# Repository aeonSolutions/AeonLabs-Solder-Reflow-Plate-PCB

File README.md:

[PCB-Prototyping-Catalogue](https://github.com/aeonSolutions/PCB-Prototyping-Catalogue)  >>  [DIY & Maker](https://github.com/aeonSolutions/PCB-Prototyping-Catalogue/blob/main/DIY-Maker/README.md)  >> Solder Reflow Plate PCB

<br>

<br />

# Solder Reflow Plate PCB
 Improved Kicad PCB schematics for a DIY Solder Reflow Plate from the original pcb schematic by [AfterEarthLTD](https://github.com/AfterEarthLTD/Solder-Reflow-Plate). AeonLabs Solder Reflow Plate features a Nextion 3.2" LCD Touch and a ESP32 WROOM32 for WiFi and Bluetooth connectivity. 

*Don't forget to LIKE , SHARE and subscribe the free whatsApp group* and if you liked this PCB consider buying me a cup of coffee. Links below.

### Status
  Revision 1.3 needs to cross TX/RX pads or else fails with "no serial data ..."

 revision 2.0 waiting to be tested.

If you have already tested this PCB send me a message.

## Versions
### AeonLabs improved Hot Solder Reflow Plate
- revision 2.x (ToDo)
  - Firmware code for the ESP32 WROOM32 and for the Nextion 3.2" LCD Touch on this Solder Reflow Plate
  - Android App to view and control the hot plate temperature

- revision 2.0
  - Serial TX/RX track lines correction.
  - Added an ON/ OFF switch 
  - Redesigned and new 5.0V and 3.3V power managment for more than 90% efficiency . No more hot LDOs on the PCB! 
 
- revison 1.x
  - Upgraded to ZLDO1117 voltage regulators with copper heat dissipation area
  - ESP32 MCU with BLE and WiFi
  - 2x Temperature seensors for improved management of Reflow temperature
  - 12VDC (5A Minimum)
  - 5.5mm x 2.5mm Barrel Jack
  - With corner M7.5 holes for placement of an aluminium plate on top of the PCB for extended lifetime and durability
  - Electronic components placed on the bottom side for extended lifetime and improved duraility
  - Aluminium plate can now be exported as Gerber to [FlatCAM](http://flatcam.org) and drilled using [Candle](https://github.com/Denvi/Candle) 

<p align="center">
  
  </p>

### *FlatCAM settings*
 
One can CNC the aluminium base plate on any GBRL CNC machine like this one on AliExpress [here](https://s.click.aliexpress.com/e/_AOOXQ7). Don't forget to use a thin lubricating oil for improved results. 
 
  - Feed Rate: 0.3-0.5 units/min
  - Depth pass: 1.1 mm or 0.04331 inch (unless your setup your CNC with Z-height correction; for a 8mm thick aluminium plate)
  - Tool [CNC Single Flute Milling cutters for Aluminum](https://www.aliexpress.com/item/1005004188243213.html?spm=a2g0o.cart.0.0.3cb23c00L4Ibog&mp=1): 2mm or 0.07874 inch
  - pass overlap: 0.0
  
 ________________________________________________________________________________________________________________

### Regular Hot Solder Reflow Plate as seen on GreatScott
- revision 1.0
  - 120mm x 70mm (Bigger hot plate dimensions)
  - 12VDC (5A Minimum)
  - 5.5mm x 2.5mm Barrel Jack
  - 0.91" OLED Display
  - Atmel Mega 328P MCU (this version includes a crystal for programming)
  - With corner M2.5 holes for placement of an aluminium plate on top of the PCB for extended lifetime and durability.

## As Seen On GreatScott! 
This is the Gerber & KiCad files for the Youtuber GreatScott! video "The Best way to reflow solder? Hot Plate to the rescue! DIY or Buy"
Check it out here - [The Best way to reflow solder? Hot Plate to the rescue! DIY or Buy](https://www.youtube.com/watch?v=QarizoUnRfk)

You have 2 options:

Download this repository for the KiCad Files or, download the Gerber files in the release section of this repository

### alternatively if you do not want to build a PCB by yourself, you can buy here:

<p align="center">
  
</p>

The price will be around 30eur plus postage fees.
(I will also deliver the assembled PCB with all the components in place at an aditonal cost).

## Liked it ? Get a Free PCB for yourself
Send me your device or hardware and i will design a custom PCB for it. Free of charge. Contact-me on WhatsApp or email for more info. 

|  | *Don't forget to **LIKE** , **SHARE** and **subscribe** the free chat groups* and if you downloaded one of AeonLabs's PCBs consider sponsor  any open hardware project with a donation or a cup of coffee. Links on the top, right side pane and below. |
|-------------|------|

<br />
<br />

## Q&A WhatsApp/Telegram Groups
|  | Subscribe to the WhatsApp or Telegram channel to get latest information about any of this KiCad projects and get help. Or simply like this kind of projects and want to stay updated with the latest research ideas and prototypes during the day and week.   |
|-------------|------|

<br />
<br />
<br />

## Youtube Channel
|  | Subscribe to my Youtube channel for PCB assembly instruction or any other related to Artificial Intelligence, Smart devices and robotics. Link to the channel [here](https://www.youtube.com/channel/UCAewCBpMRPGCyFc1ET5CHJw). My most recent video is .... |
|-------------|------|

#### PCB Parts list:
- 1x AMS1117-3.3, sold on AliExpress [here](https://s.click.aliexpress.com/e/_AOIVLN)
- 1x AMS1117-5.0, sold on AliExpress [here](https://s.click.aliexpress.com/e/_AOIVLN)
- 1x FUSE SMD 1206 5A, sold on AliExpress [here](https://s.click.aliexpress.com/e/_A8yVgJ)
- 1x MM1Z24, sold on AliExpress [here](https://www.aliexpress.com/item/1005003538876461.html?spm=a2g0o.order_list.0.0.2bb91802tqEyK1)
- Barrel Jack, sold on AliExpress [here](https://s.click.aliexpress.com/e/_As3F2L)
- 1x FPC 1x4 pin 1mm pitch horizontal, sold on AliExpress [here](https://s.click.aliexpress.com/e/_ASMTDp)
- 1x FPC flat cable 1mm pitch 4 pin, sold on AliExpress [here](https://s.click.aliexpress.com/e/_9js0C7)
- 1x DSR1M, sold on AliExpress [here](https://s.click.aliexpress.com/e/_9JQobh)
- 1x SMAJ18A, sold on AliExpress [here](https://s.click.aliexpress.com/e/_9zW0DN)
- 2x LMT85LP, sold on AliExpress [here](https://www.aliexpress.com/item/1005003755656556.html?spm=a2g0o.order_list.0.0.42ba1802MVKTRu)
- 1x UMW30N06, sold on AliExpress [here](https://www.aliexpress.com/item/4000687585069.html?spm=a2g0o.order_list.0.0.2bb91802tqEyK1)
- 1x ESP32 WROOM32, sold on AliExpress [here](https://www.aliexpress.com/item/32912371635.html?spm=a2g0o.productlist.0.0.1c737b00qtI6F1&algo_pvid=2b9d3923-cad6-4894-abba-bcbe1659aab6&algo_exp_id=2b9d3923-cad6-4894-abba-bcbe1659aab6-0&pdp_ext_f=%7B"sku_id"%3A"65986896288"%7D&pdp_npi=2%40dis%21EUR%21%212.27%21%21%21%21%21%400bb0622916528901078995704e092a%2165986896288%21sea)
- 1x NEXTION 3.2" LCD Touch, sold on AliExpress [here](https://www.aliexpress.com/item/32678581956.html?spm=a2g0o.productlist.0.0.16f46e8cmt3XbA&algo_pvid=657314cc-0888-4621-8795-71fcd735d410&algo_exp_id=657314cc-0888-4621-8795-71fcd735d410-2&pdp_ext_f=%7B%22sku_id%22%3A%2210000003437337029%22%7D&pdp_npi=2%40dis%21EUR%21%2126.15%21%21%21%21%21%40210318b916528902149054769e34ce%2110000003437337029%21sea)

<br />
<br />

## Author

You can get in touch with me on my LinkedIn Profile:

#### Miguel Tomas

You can also follow my GitHub Profile to stay updated about my latest projects: 

<br>

**Hire me** <br>
See [here](https://github.com/aeonSolutions/PCB-Prototyping-Catalogue/wiki/How-to-Hire-AeonLabs) how to hire AeonLabs.

<br>

### Be supportive of my dedication and work towards technology education and buy me a cup of coffee
The PCB design Files I provide here for anyone to use are free. If you like this Smart Device or use it, please consider buying me a cup of coffee, a slice of pizza or a book to help me study, eat and think new PCB design files.

<p align="center">
    
</p>

### Make a donation on PayPal
Make a donation on PayPal and get a TAX refund*.

<p align="center">
    
</p>

### Support all these open hardware projects and become a GitHub sponsor  
Liked any of my PCB KiCad Designs? Help and Support my open work to all by becoming a GitHub sponsor.

<p align="center">

</p>

# 

### License

Before proceeding to download any of AeonLabs software solutions for open-source development and/or PCB hardware electronics development make sure you are choosing the right license for your project. See [AeonLabs Solutions for Open Hardware & Source Development](https://github.com/aeonSolutions/PCB-Prototyping-Catalogue/wiki/AeonLabs-Solutions-for-Open-Hardware-&-Source-Development) for more information.

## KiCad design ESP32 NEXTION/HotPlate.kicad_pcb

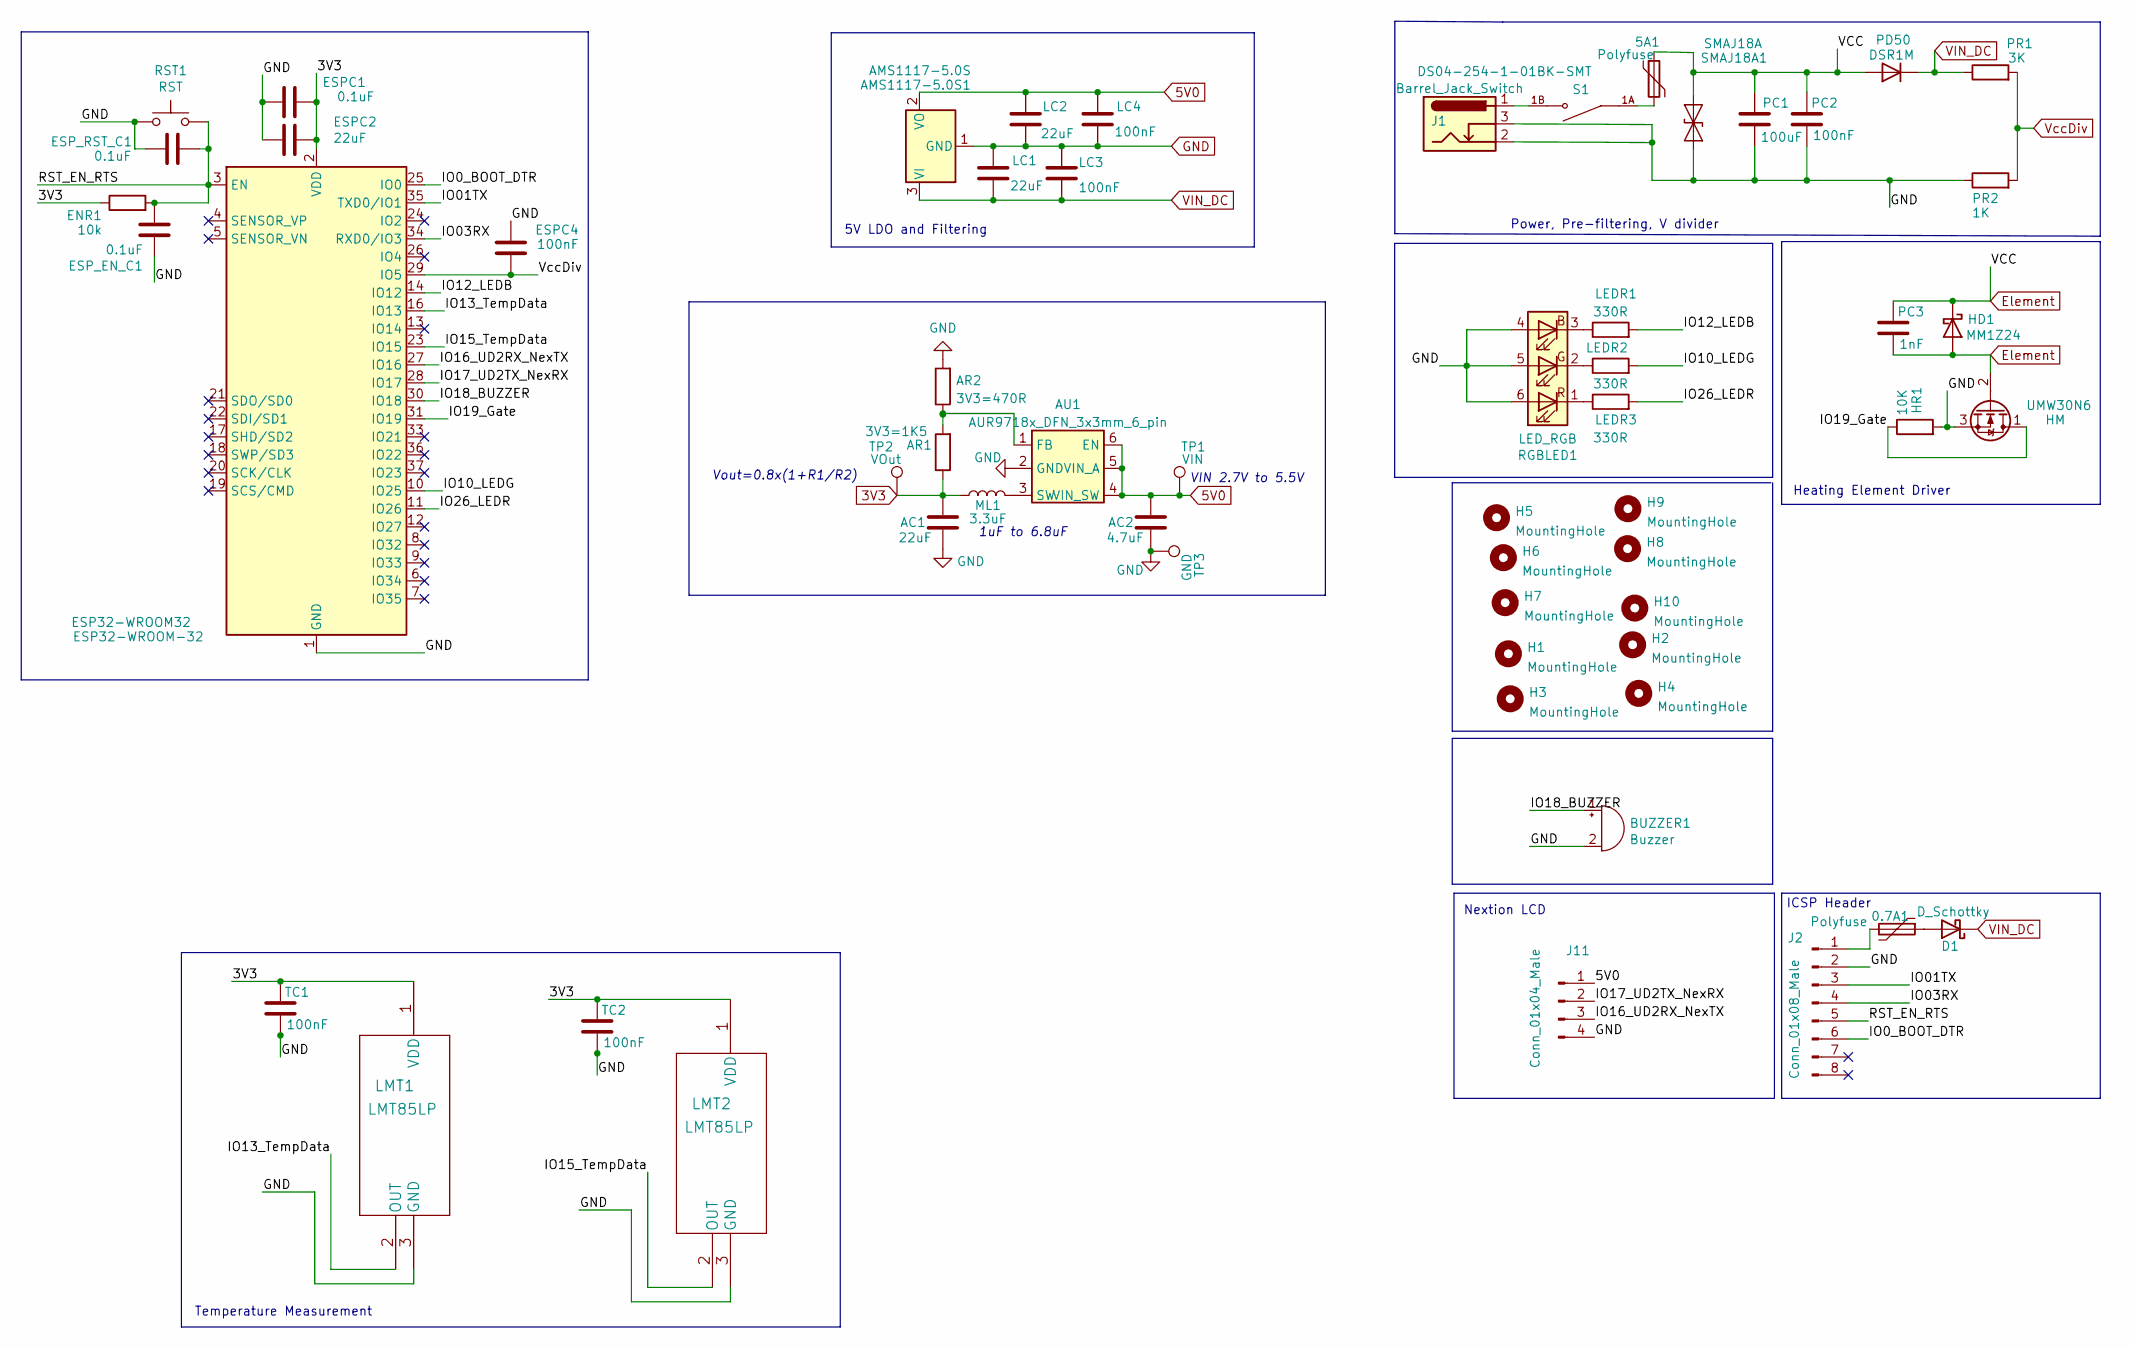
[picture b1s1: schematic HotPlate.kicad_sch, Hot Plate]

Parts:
0.7A1, 5A1: Polyfuse; Fuse_1206_3216Metric
AC1: 22uF; C_0805_2012Metric_Pad1.18x1.45mm_HandSolder
AC2: 4.7uF; C_0805_2012Metric_Pad1.18x1.45mm_HandSolder
AMS1117-5.0S1: AMS1117-5.0S; SOT-223-3_TabPin2
AR1: 3V3=1K5; R_0805_2012Metric_Pad1.20x1.40mm_HandSolder
AR2: 3V3=470R; R_0805_2012Metric_Pad1.20x1.40mm_HandSolder
AU1: AUR9718x_DFN_3x3mm_6_pin; AUR9718 3x3mm 6 pin
BUZZER1: Buzzer; MagneticBuzzer_Kobitone_254-EMB84Q-RO
D1: D_Schottky; D_1210_3225Metric_Pad1.42x2.65mm_HandSolder
ENR1: 10k; R_1206_3216Metric
ESP32-WROOM32: ESP32-WROOM-32
ESPC1: 0.1uF; C_1206_3216Metric
ESPC2: 22uF; C_1206_3216Metric
ESPC4: 100nF; C_1206_3216Metric
ESP_EN_C1: 0.1uF; C_1206_3216Metric
ESP_RST_C1: 0.1uF; C_1206_3216Metric
H1, H2, H3, H4: MountingHole; MountingHole_3.2mm_M3
H5, H6, H7, H8, H9, H10: MountingHole; MountingHole_8.4mm_M8
HD1: MM1Z24; D_SOD-123
HR1: 10K; C_1206_3216Metric_Pad1.33x1.80mm_HandSolder
J1: Barrel_Jack_Switch; BarrelJack_Horizontal
J2: Conn_01x08_Male; SOIC_clipProgSmall
J11: Conn_01x04_Male; Molex_200528-0040_1x04-1MP_P1.00mm_Horizontal
LC1, LC2: 22uF; C_1206_3216Metric_Pad1.33x1.80mm_HandSolder
LC3, LC4: 100nF; C_1206_3216Metric_Pad1.33x1.80mm_HandSolder
LEDR1, LEDR2, LEDR3: 330R; R_1206_3216Metric
LMT1, LMT2: LMT85LP
ML1: 3.3uF; L_1210_3225Metric
PC1: 100uF; CP_Elec_10x12.5
PC2: 100nF; C_1206_3216Metric_Pad1.33x1.80mm_HandSolder
PC3: 1nF; C_1206_3216Metric_Pad1.33x1.80mm_HandSolder
PD50: DSR1M; D_SOD-123F
PR1: 3K; C_1206_3216Metric_Pad1.33x1.80mm_HandSolder
PR2: 1K; C_1206_3216Metric_Pad1.33x1.80mm_HandSolder
RGBLED1: LED_RGB; LED_RGB_5050-6
RST1: RST; SW_Push_SPST_NO_Alps_SKRK
S1: DS04-254-1-01BK-SMT; Side Switch 3pin 5A; PARTREV V0.0
SMAJ18A1: SMAJ18A; D_1210_3225Metric_Pad1.42x2.65mm_HandSolder
TC1, TC2: 100nF; C_1206_3216Metric_Pad1.33x1.80mm_HandSolder
TP1: VIN; TestPoint_Pad_D1.0mm
TP2: VOut; TestPoint_Pad_D1.0mm
TP3: GND; TestPoint_Pad_D1.0mm
UMW30N6: HM; TO-252-2

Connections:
3V3: AC1.1, AR1.1, ENR1.1, ESP32-WROOM32.2 (VDD), ESPC1.1, ESPC2.1, LMT1.1 (VDD), LMT2.1 (VDD), ML1.1, TC1.1, TC2.1, TP2.1
5V0: AC2.1, AMS1117-5.0S1.2 (VO), AU1.4 (VIN_SW), AU1.5 (VIN_A), AU1.6 (EN), J11.1, LC2.1, LC4.1, TP1.1
/IO0_BOOT_DTR: ESP32-WROOM32.25 (IO0), J2.6
/IO01TX: ESP32-WROOM32.35 (TXD0/IO1), J2.3
/IO03RX: ESP32-WROOM32.34 (RXD0/IO3), J2.4
/IO10_LEDG: ESP32-WROOM32.10 (IO25), LEDR2.2
/IO12_LEDB: ESP32-WROOM32.14 (IO12), LEDR1.2
/IO13_TempData: ESP32-WROOM32.16 (IO13), LMT1.2 (OUT)
/IO15_TempData: ESP32-WROOM32.23 (IO15), LMT2.2 (OUT)
/IO16_UD2RX_NexTX: ESP32-WROOM32.27 (IO16), J11.3
/IO17_UD2TX_NexRX: ESP32-WROOM32.28 (IO17), J11.2
/IO18_BUZZER: BUZZER1.1 (-), ESP32-WROOM32.30 (IO18)
/IO19_Gate: ESP32-WROOM32.31 (IO19), HR1.1, UMW30N6.1 (D)
/IO26_LEDR: ESP32-WROOM32.11 (IO26), LEDR3.2
/RST_EN_RTS: ENR1.2, ESP32-WROOM32.3 (EN), ESP_EN_C1.2, ESP_RST_C1.1, J2.5, RST1.2
Element: 5A1.1, HD1.1 (K), HD1.2 (A), PC1.1, PC2.1, PC3.1, PC3.2, PD50.2 (A), SMAJ18A1.1 (A1), UMW30N6.2 (G)
GND: AC1.2, AC2.2, AMS1117-5.0S1.1 (GND), AR2.2, AU1.2 (GND), BUZZER1.2 (+), ESP32-WROOM32.1 (GND), ESP32-WROOM32.15 (GND), ESP32-WROOM32.38 (GND), ESP32-WROOM32.39 (GND), ESPC1.2, ESPC2.2, ESPC4.2, ESP_EN_C1.1, ESP_RST_C1.2, HR1.2, J1.2, J1.3, J2.2, J11.4, LC1.1, LC2.2, LC3.1, LC4.2, LMT1.3 (GND), LMT2.3 (GND), PC1.2, PC2.2, PR2.1, RGBLED1.4 (BA), RGBLED1.5 (GA), RGBLED1.6 (RA), RST1.1, SMAJ18A1.2 (A2), TC1.2, TC2.2, TP3.1, UMW30N6.3 (S)
unnamed: 0.7A1.1, D1.2 (A)
unnamed: 0.7A1.2, J2.1
unnamed: 5A1.2, S1.1A
unnamed: AR1.2, AR2.1, AU1.1 (FB)
unnamed: AU1.3 (SW), ML1.2
unnamed: J1.1, S1.1B
unnamed: LEDR1.1, RGBLED1.3 (BK)
unnamed: LEDR2.1, RGBLED1.2 (GK)
unnamed: LEDR3.1, RGBLED1.1 (RK)
VIN_DC: AMS1117-5.0S1.3 (VI), D1.1 (K), LC1.2, LC3.2, PD50.1 (K), PR1.1
VccDiv: ESP32-WROOM32.29 (IO5), ESPC4.1, PR1.2, PR2.2

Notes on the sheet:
Power, Pre-filtering, V divider
ICSP Header
Vout=0.8x(1+R1/R2)
Temperature Measurement
Heating Element Driver
1uF to 6.8uF
5V LDO and Filtering
Nextion LCD
VIN 2.7V to 5.5V

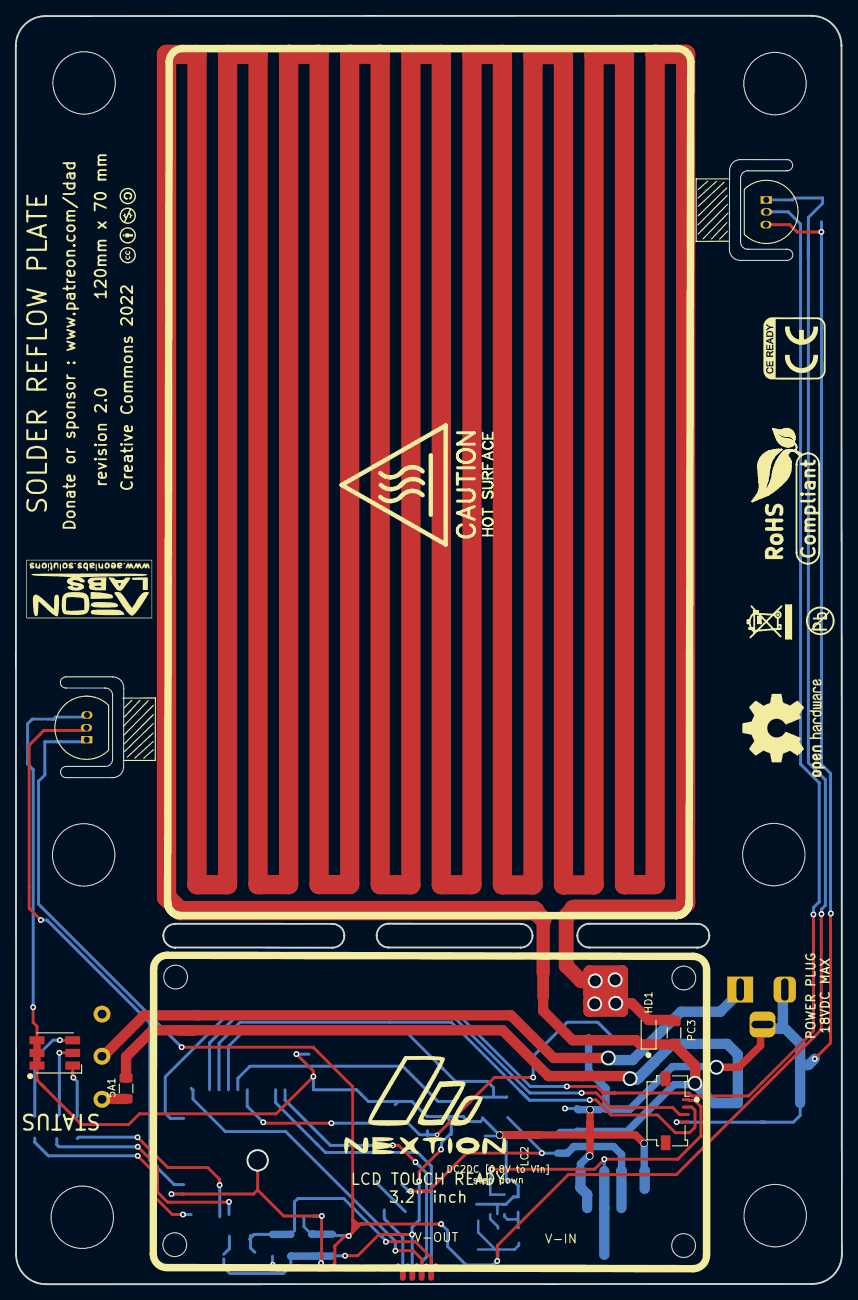
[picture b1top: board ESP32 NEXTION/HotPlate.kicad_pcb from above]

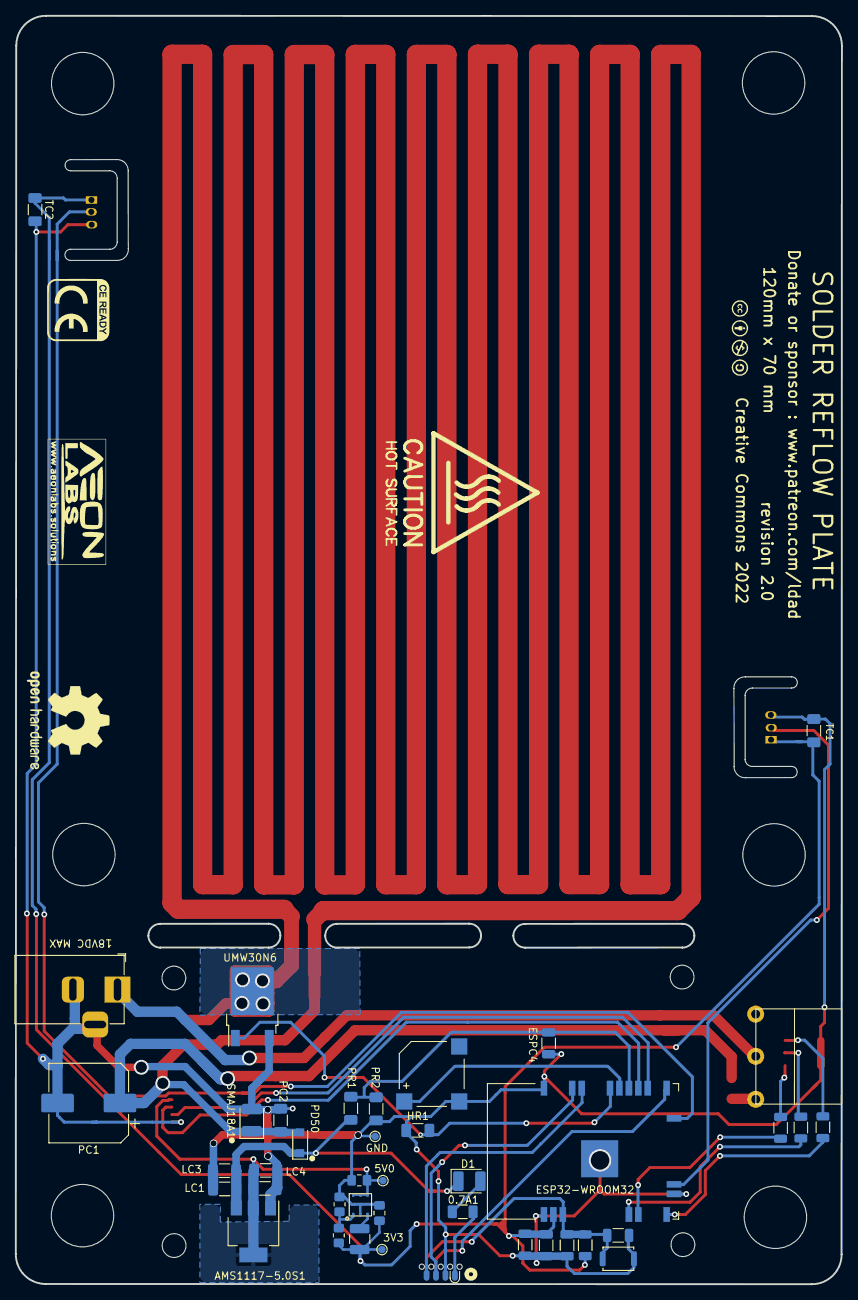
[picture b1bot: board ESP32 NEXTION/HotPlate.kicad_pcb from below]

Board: 6 copper layers, 111.2 x 170.7 mm, 61 parts (41 on the bottom side), 28 nets.

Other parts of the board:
Sign-PbFree: LOGO_PBFREE
Sign-RecycleBin: LOGO_RECYCLEBIN_1
Sign-RoHS: LOGO_ROHS_1

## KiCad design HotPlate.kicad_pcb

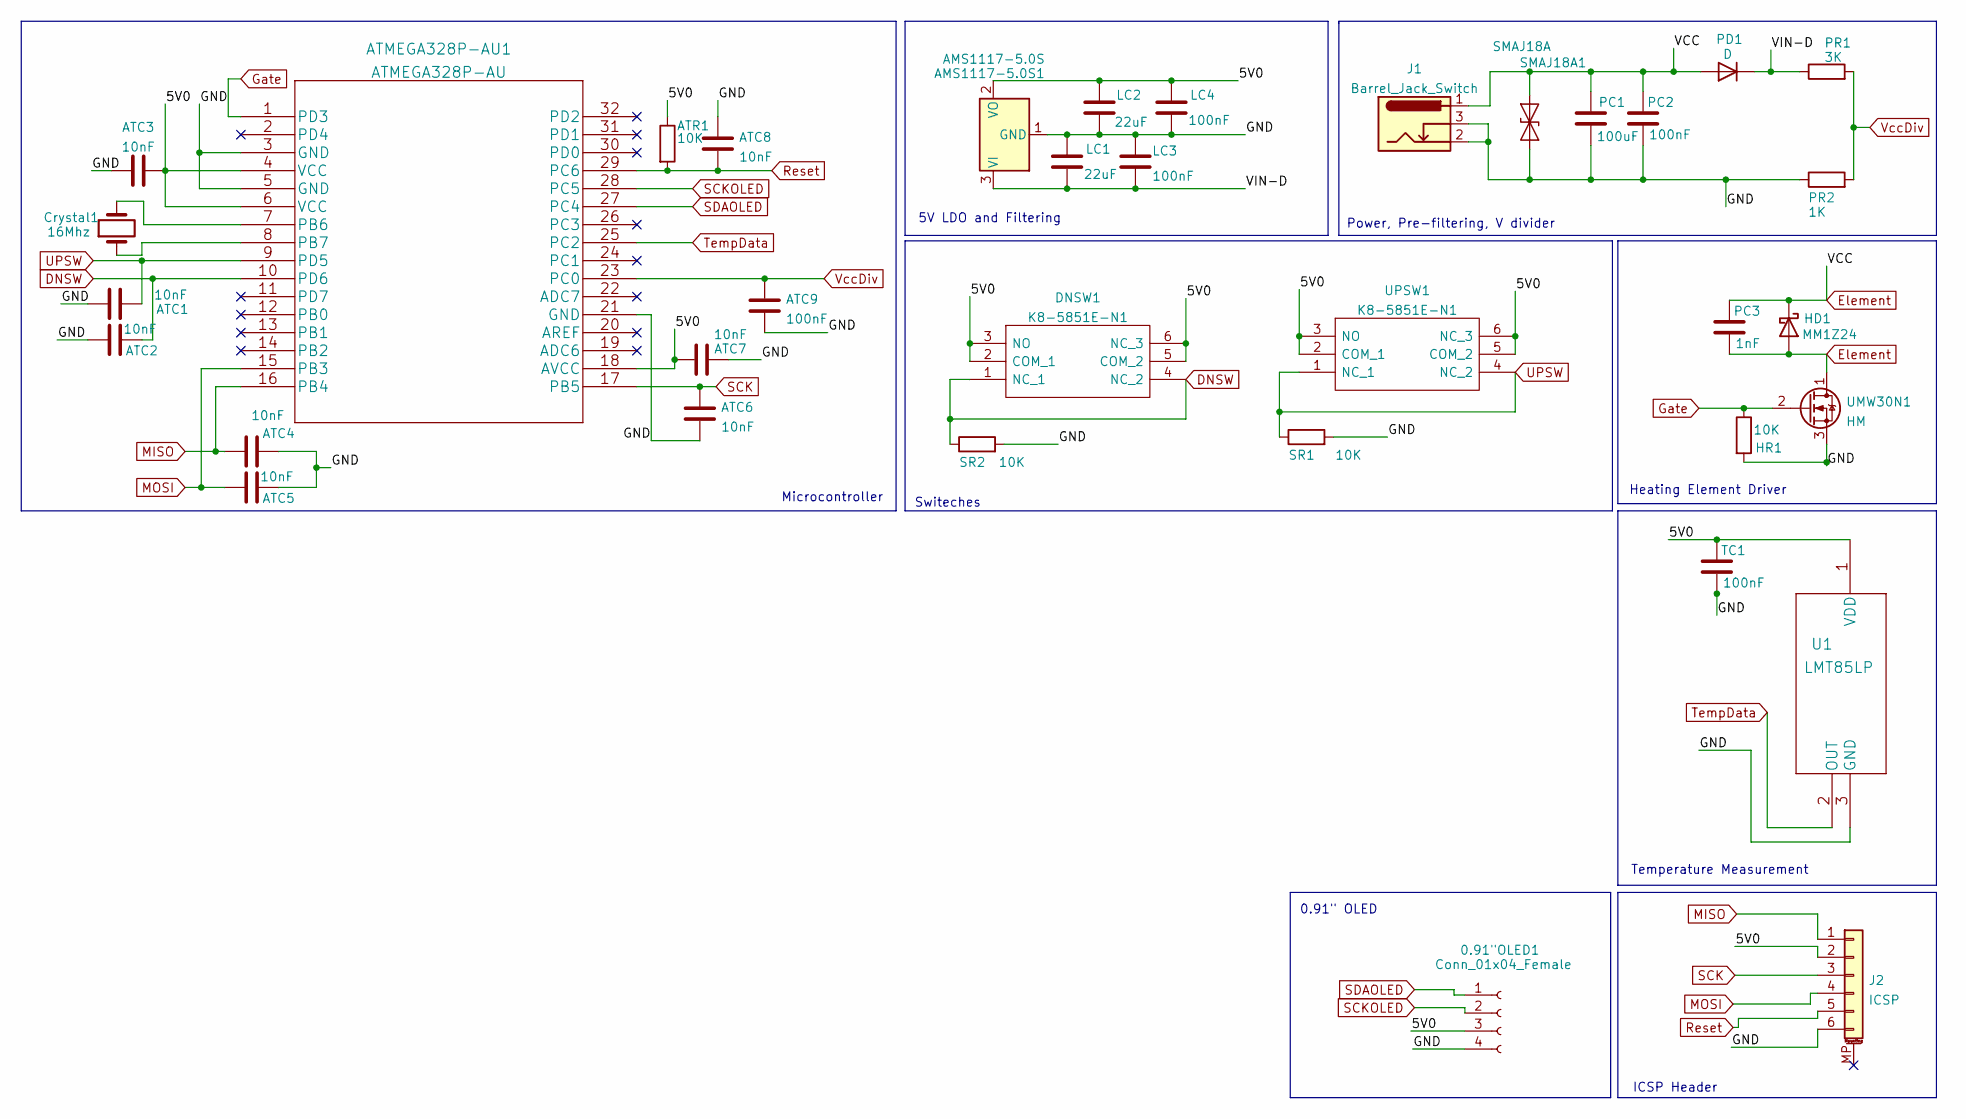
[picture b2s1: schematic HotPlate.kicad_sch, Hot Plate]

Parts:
0.91"OLED1: Conn_01x04_Female; SSD1306-0.91-OLED-4pin-128x32
AMS1117-5.0S1: AMS1117-5.0S; SOT-223-3_TabPin2
ATC1, ATC2, ATC3, ATC4, ATC5, ATC6, ATC7, ATC8: 10nF; C_1206_3216Metric_Pad1.33x1.80mm_HandSolder
ATC9: 100nF; C_1206_3216Metric_Pad1.33x1.80mm_HandSolder
ATMEGA328P-AU1: ATMEGA328P-AU
ATR1: 10K; R_1206_3216Metric
Crystal1: 16Mhz; Crystal_SMD_5032-2Pin_5.0x3.2mm
DNSW1: K8-5851E-N1; K85851EN1; Manufacturer_Part_Number K8-5851E-N1
HD1: MM1Z24
HR1: 10K; C_1206_3216Metric_Pad1.33x1.80mm_HandSolder
J1: Barrel_Jack_Switch; BarrelJack_Horizontal
J2: ICSP; PinHeader_2x03_P2.54mm_Vertical
LC1, LC2: 22uF; C_1206_3216Metric_Pad1.33x1.80mm_HandSolder
LC3, LC4: 100nF; C_1206_3216Metric_Pad1.33x1.80mm_HandSolder
PC1: 100uF; CP_Elec_6.3x5.9
PC2: 100nF; C_1206_3216Metric_Pad1.33x1.80mm_HandSolder
PC3: 1nF; C_1206_3216Metric_Pad1.33x1.80mm_HandSolder
PD1: D; D_SOD-123
PR1: 3K; C_1206_3216Metric_Pad1.33x1.80mm_HandSolder
PR2: 1K; C_1206_3216Metric_Pad1.33x1.80mm_HandSolder
SMAJ18A1: SMAJ18A; D_SOD-123
SR1, SR2: 10K; C_1206_3216Metric_Pad1.33x1.80mm_HandSolder
TC1: 100nF; C_1206_3216Metric_Pad1.33x1.80mm_HandSolder
U1: LMT85LP
UMW30N1: HM
UPSW1: K8-5851E-N1; K85851EN1; Manufacturer_Part_Number K8-5851E-N1

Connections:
/5V0: 0.91"OLED1.3, AMS1117-5.0S1.2 (VO), ATC3.2, ATC7.1, ATMEGA328P-AU1.4 (VCC), ATMEGA328P-AU1.6 (VCC), ATMEGA328P-AU1.18 (AVCC), ATR1.1, DNSW1.2 (COM_1), DNSW1.3 (NO), DNSW1.5 (COM_2), DNSW1.6 (NC_3), J2.2, LC2.1, LC4.1, TC1.1, U1.1 (VDD), UPSW1.2 (COM_1), UPSW1.3 (NO), UPSW1.5 (COM_2), UPSW1.6 (NC_3)
/GND: 0.91"OLED1.4, AMS1117-5.0S1.1 (GND), ATC1.1, ATC2.1, ATC3.1, ATC4.2, ATC5.2, ATC6.2, ATC7.2, ATC8.1, ATC9.2, ATMEGA328P-AU1.3 (GND), ATMEGA328P-AU1.5 (GND), ATMEGA328P-AU1.21 (GND), HR1.2, J1.2, J1.3, J2.6, LC1.1, LC2.2, LC3.1, LC4.2, PC1.2, PC2.2, PR2.1, SMAJ18A1.1 (A1), SR1.2, SR2.2, TC1.2, U1.3 (GND), UMW30N1.3 (S)
/VIN-D: AMS1117-5.0S1.3 (VI), LC1.2, LC3.2, PD1.1 (K), PR1.1
DNSW: ATC2.2, ATMEGA328P-AU1.10 (PD6), DNSW1.1 (NC_1), DNSW1.4 (NC_2), SR2.1
Element: HD1.1 (K), HD1.2 (A), J1.1, PC1.1, PC2.1, PC3.1, PC3.2, PD1.2 (A), SMAJ18A1.2 (A2), UMW30N1.1 (D)
Gate: ATMEGA328P-AU1.1 (PD3), HR1.1, UMW30N1.2 (G)
MISO: ATC4.1, ATMEGA328P-AU1.16 (PB4), J2.1
MOSI: ATC5.1, ATMEGA328P-AU1.15 (PB3), J2.4
unnamed: ATMEGA328P-AU1.7 (PB6), Crystal1.2
unnamed: ATMEGA328P-AU1.8 (PB7), Crystal1.1
Reset: ATC8.2, ATMEGA328P-AU1.29 (PC6), ATR1.2, J2.5
SCK: ATC6.1, ATMEGA328P-AU1.17 (PB5), J2.3
SCKOLED: 0.91"OLED1.2, ATMEGA328P-AU1.28 (PC5)
SDAOLED: 0.91"OLED1.1, ATMEGA328P-AU1.27 (PC4)
TempData: ATMEGA328P-AU1.25 (PC2), U1.2 (OUT)
UPSW: ATC1.2, ATMEGA328P-AU1.9 (PD5), SR1.1, UPSW1.1 (NC_1), UPSW1.4 (NC_2)
VccDiv: ATC9.1, ATMEGA328P-AU1.23 (PC0), PR1.2, PR2.2

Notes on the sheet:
Power, Pre-filtering, V divider
Microcontroller
ICSP Header
Temperature Measurement
Heating Element Driver
5V LDO and Filtering
0.91" OLED
Switeches

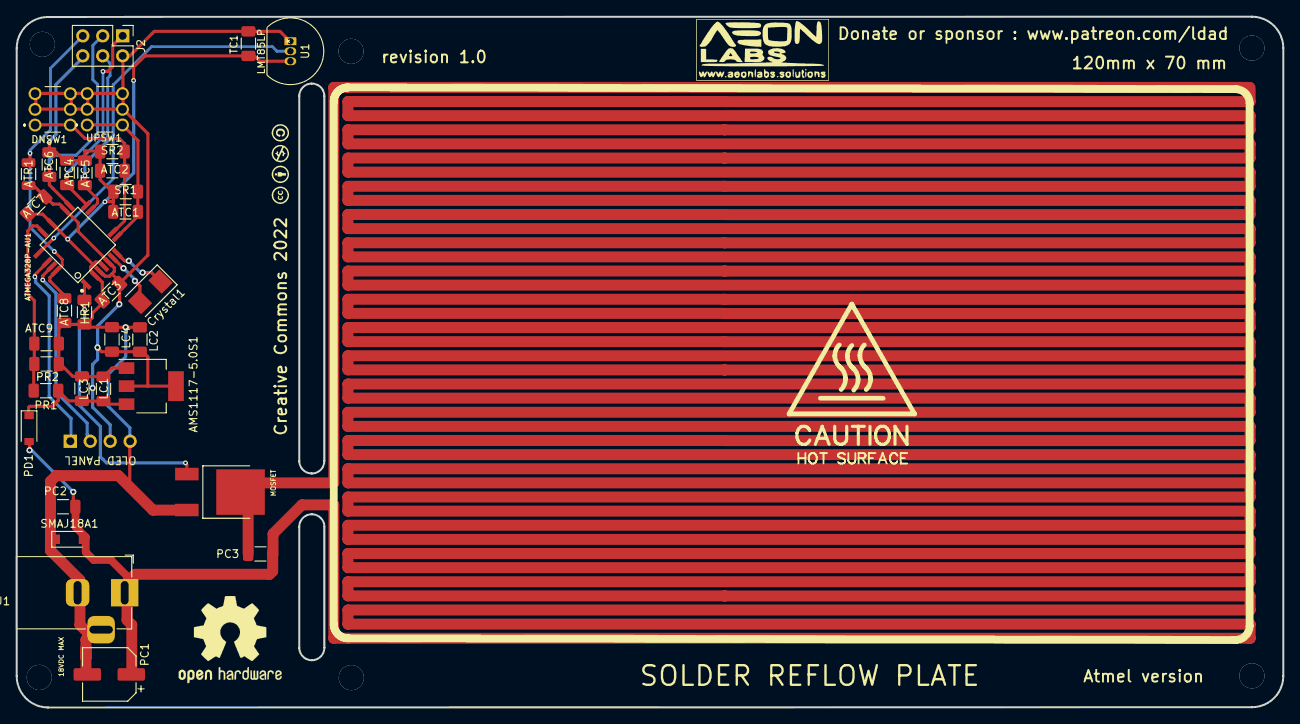
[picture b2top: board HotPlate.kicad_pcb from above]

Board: 2 copper layers, 161.4 x 88.0 mm, 35 parts (1 on the bottom side), 17 nets.

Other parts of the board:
MOSFET: UMW30N06; TO-252-2_L6.6-W6.1-P4.57-LS9.9-BR-CW

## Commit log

2022-02-28 main
2022-02-28 added code for the atmel
2022-04-30 rev. 1.2
2022-04-30 revision 1.2
2022-05-18 aluminium base update
2022-05-27 revision 1.3
2022-05-31 revision update
2022-06-21 revision update
    Added some HiRes cool phtoos
2022-08-18 rev. 2.0
    added ON/OFF switch

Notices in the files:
ESP32 NEXTION/HotPlate.kicad_pcb:
Creative Commons 2022
parts and their libraries:
Copyright 2021 Accelerated Designs. All rights reserved.
